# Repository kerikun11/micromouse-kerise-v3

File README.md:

# MicroMouse KERISE v3

ハーフサイズマイクロマウス

## 戦績

- 第38回全日本マイクロマウス大会2017
  - ハーフサイズ競技エキスパートクラス予選13位
  - ハーフサイズ競技エキスパートクラス決勝13位
  - ハーフサイズ競技エキスパートクラス特別賞

## スペック

| 部品             | 型番        | 備考                              |
| :--------------- | :---------- | :-------------------------------- |
| モーター         | 不明        | 直径6mm 長さ10mm コアレスモーター |
| エンコーダ       | AS5048A     | 4096パルス 磁気式                 |
| マイコン         | ESP32-D0WD  | 240MHz dual core                  |
| 赤外線LED        | VSMB294008G | 波長940mm                         |
| フォトダイオード | VEMD2020X01 | 波長940nm                         |
| モータードライバ | DRV8835     | 最大電流1.5A x 2ch                |
| 6軸センサ        | ICM-20602   | 3軸ジャイロ+3軸加速度             |
| バッテリー       | 不明        | 3.7V 25C 100mAh 1S                |

## 回路設計

- KiCad

## 開発環境

- ESP-IDF

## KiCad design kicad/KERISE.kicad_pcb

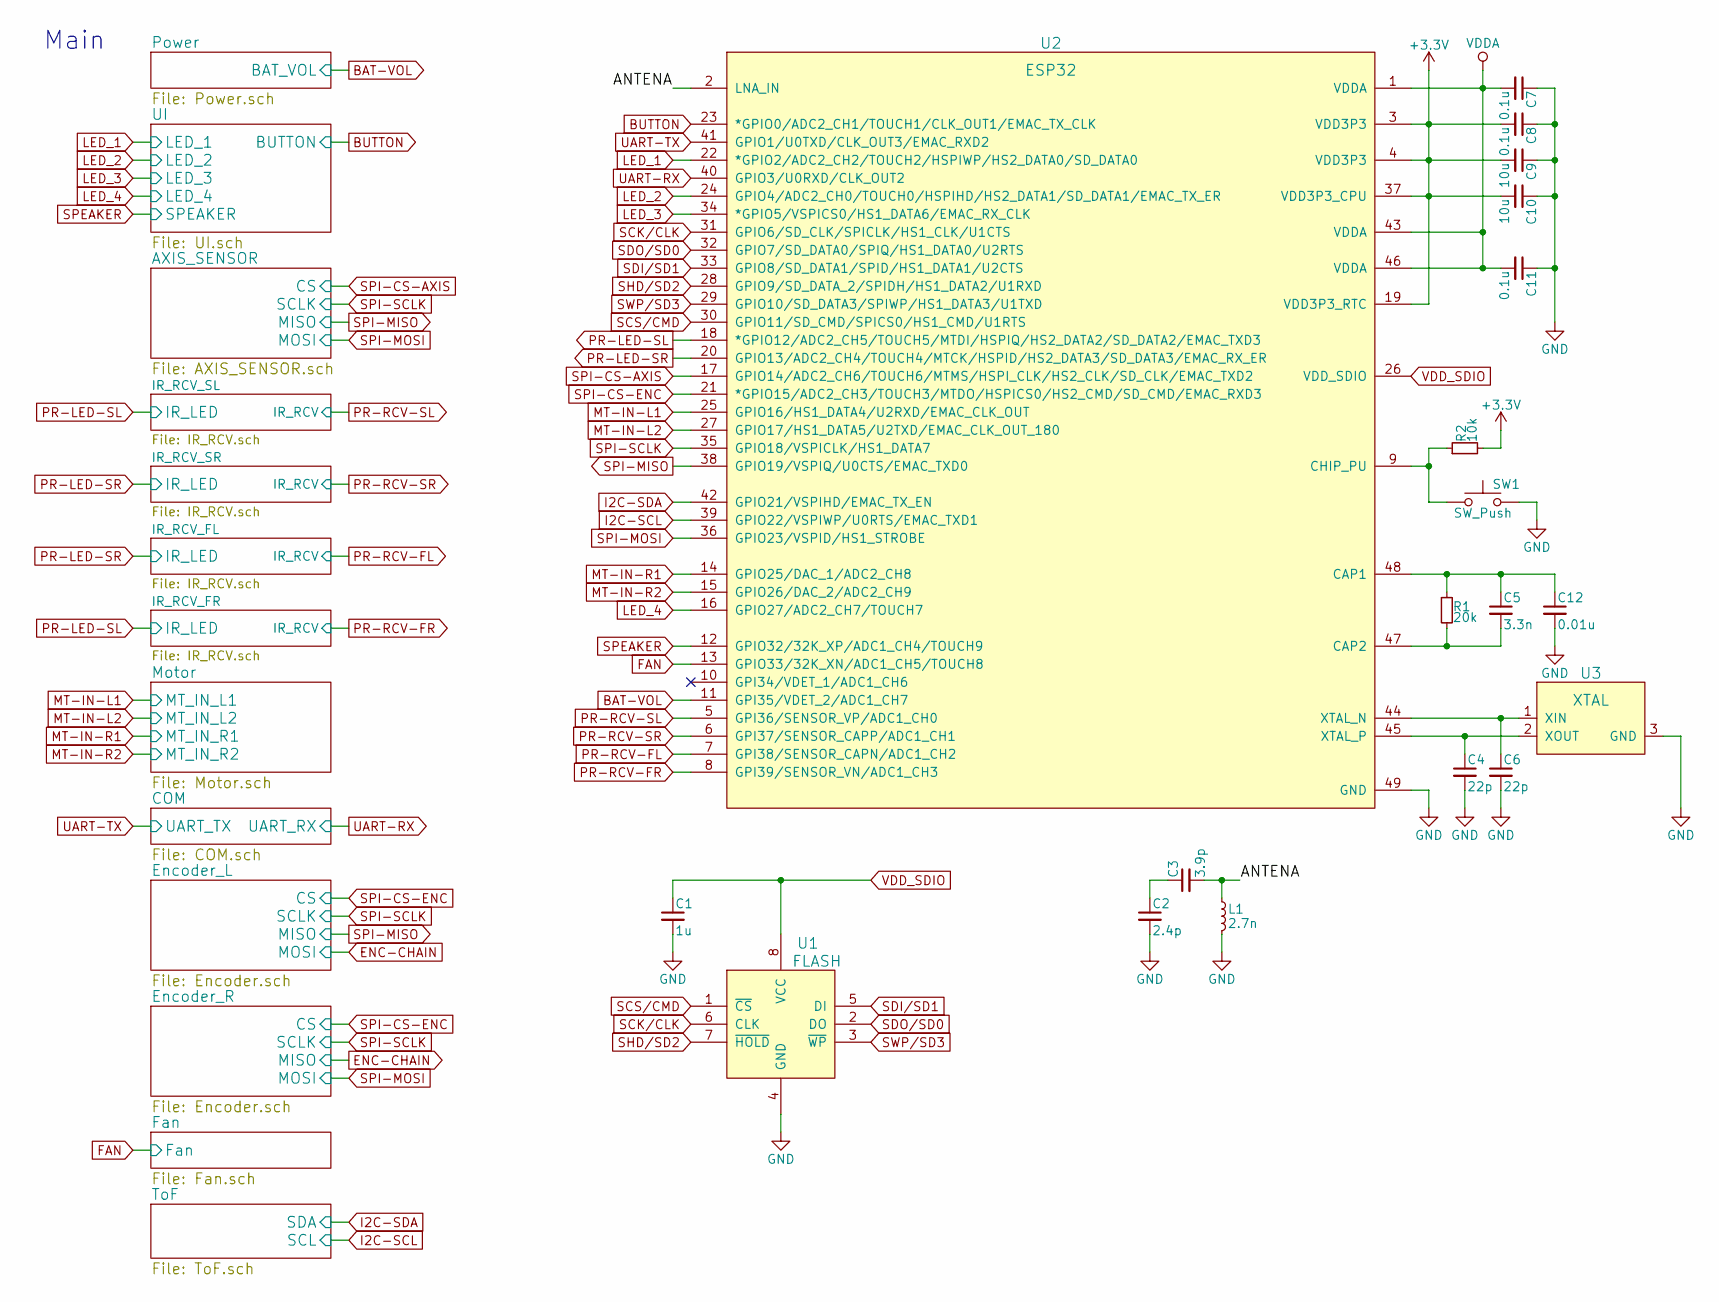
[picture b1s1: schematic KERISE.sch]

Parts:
C1: 1u; C_0402
C2: 2.4p; C_0201
C3: 3.9p; C_0201
C4, C6: 22p; C_0201
C5: 3.3n; C_0201
C7, C8, C11: 0.1u; C_0201
C9, C10: 10u; C_0402
C12: 0.01u; C_0201
L1: 2.7n; C_0201
R1: 20k; R_0201
R2: 10k; R_0201
SW1: SW_Push; SW_PUSH
U1: FLASH; SOIJ-8_5.3x5.3mm_Pitch1.27mm
U2: ESP32
U3: XTAL; crystal_FA238-TSX3225

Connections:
+3V3: C8.2, C9.2, C10.2, R2.2, U2.3 (VDD3P3), U2.4 (VDD3P3), U2.19 (VDD3P3_RTC), U2.37 (VDD3P3_CPU); also elsewhere on the board
/ANTENA: C3.2, L1.1, U2.2 (LNA_IN)
BAT-VOL: U2.11 (GPI35/VDET_2/ADC1_CH7); also elsewhere on the board
BUTTON: U2.23 (*GPIO0/ADC2_CH1/TOUCH1/CLK_OUT1/EMAC_TX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); also elsewhere on the board
FAN: U2.13 (GPIO33/32K_XN/ADC1_CH5/TOUCH8); also elsewhere on the board
GND: C1.2, C2.2, C4.2, C6.2, C7.1, C8.1, C9.1, C10.1, C11.1, C12.2, L1.2, SW1.2, U1.4 (GND), U2.49 (GND), U3.3 (GND); also elsewhere on the board
I2C-SCL: U2.39 (GPIO22/VSPIWP/U0RTS/EMAC_TXD1); also elsewhere on the board
I2C-SDA: U2.42 (GPIO21/VSPIHD/EMAC_TX_EN); also elsewhere on the board
LED_1: U2.22 (*GPIO2/ADC2_CH2/TOUCH2/HSPIWP/HS2_DATA0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); also elsewhere on the board
LED_2: U2.24 (GPIO4/ADC2_CH0/TOUCH0/HSPIHD/HS2_DATA1/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); also elsewhere on the board
LED_3: U2.34 (*GPIO5/VSPICS0/HS1_DATA6/EMAC_RX_CLK); also elsewhere on the board
LED_4: U2.16 (GPIO27/ADC2_CH7/TOUCH7); also elsewhere on the board
MT-IN-L1: U2.25 (GPIO16/HS1_DATA4/U2RXD/EMAC_CLK_OUT); also elsewhere on the board
MT-IN-L2: U2.27 (GPIO17/HS1_DATA5/U2TXD/EMAC_CLK_OUT_180); also elsewhere on the board
MT-IN-R1: U2.14 (GPIO25/DAC_1/ADC2_CH8); also elsewhere on the board
MT-IN-R2: U2.15 (GPIO26/DAC_2/ADC2_CH9); also elsewhere on the board
unnamed: C2.1, C3.1
unnamed: C4.1, U2.45 (XTAL_P), U3.2 (XOUT)
unnamed: C5.2, R1.2, U2.47 (CAP2)
unnamed: C6.1, U2.44 (XTAL_N), U3.1 (XIN)
unnamed: C5.1, C12.1, R1.1, U2.48 (CAP1)
unnamed: R2.1, SW1.1, U2.9 (CHIP_PU)
PR-LED-SL: U2.18 (*GPIO12/ADC2_CH5/TOUCH5/MTDI/HSPIQ/HS2_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); also elsewhere on the board
PR-LED-SR: U2.20 (GPIO13/ADC2_CH4/TOUCH4/MTCK/HSPID/HS2_D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); also elsewhere on the board
PR-RCV-FL: U2.7 (GPI38/SENSOR_CAPN/ADC1_CH2); also elsewhere on the board
PR-RCV-FR: U2.8 (GPI39/SENSOR_VN/ADC1_CH3); also elsewhere on the board
PR-RCV-SL: U2.5 (GPI36/SENSOR_VP/ADC1_CH0); also elsewhere on the board
PR-RCV-SR: U2.6 (GPI37/SENSOR_CAPP/ADC1_CH1); also elsewhere on the board
SCK/CLK: U1.6 (CLK), U2.31 (GPIO6/SD_CLK/SPICLK/HS1_CLK/U1CTS)
SCS/CMD: U1.1 (~CS), U2.30 (GPIO11/SD_CMD/SPICS0/HS1_CMD/U1RTS)
SDI/SD1: U1.5 (DI), U2.33 (GPIO8/SD_DATA1/SPID/HS1_DATA1/U2CTS)
SDO/SD0: U1.2 (DO), U2.32 (GPIO7/SD_DATA0/SPIQ/HS1_DATA0/U2RTS)
SHD/SD2: U1.7 (~HOLD), U2.28 (GPIO9/SD_DATA_2/SPIDH/HS1_DATA2/U1RXD)
SPEAKER: U2.12 (GPIO32/32K_XP/ADC1_CH4/TOUCH9); also elsewhere on the board
SPI-CS-AXIS: U2.17 (GPIO14/ADC2_CH6/TOUCH6/MTMS/HSPI_CLK/HS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); also elsewhere on the board
SPI-CS-ENC: U2.21 (*GPIO15/ADC2_CH3/TOUCH3/MTDO/HSPICS0/HS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); also elsewhere on the board
SPI-MISO: U2.38 (GPIO19/VSPIQ/U0CTS/EMAC_TXD0); also elsewhere on the board
SPI-MOSI: U2.36 (GPIO23/VSPID/HS1_STROBE); also elsewhere on the board
SPI-SCLK: U2.35 (GPIO18/VSPICLK/HS1_DATA7); also elsewhere on the board
SWP/SD3: U1.3 (~WP), U2.29 (GPIO10/SD_DATA3/SPIWP/HS1_DATA3/U1TXD)
UART-RX: U2.40 (GPIO3/U0RXD/CLK_OUT2); also elsewhere on the board
UART-TX: U2.41 (GPIO1/U0TXD/CLK_OUT3/EMAC_RXD2); also elsewhere on the board
VDDA: C7.2, C11.2, U2.1 (VDDA), U2.43 (VDDA), U2.46 (VDDA); also elsewhere on the board
VDD_SDIO: C1.1, U1.8 (VCC), U2.26 (VDD_SDIO)

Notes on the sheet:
Main

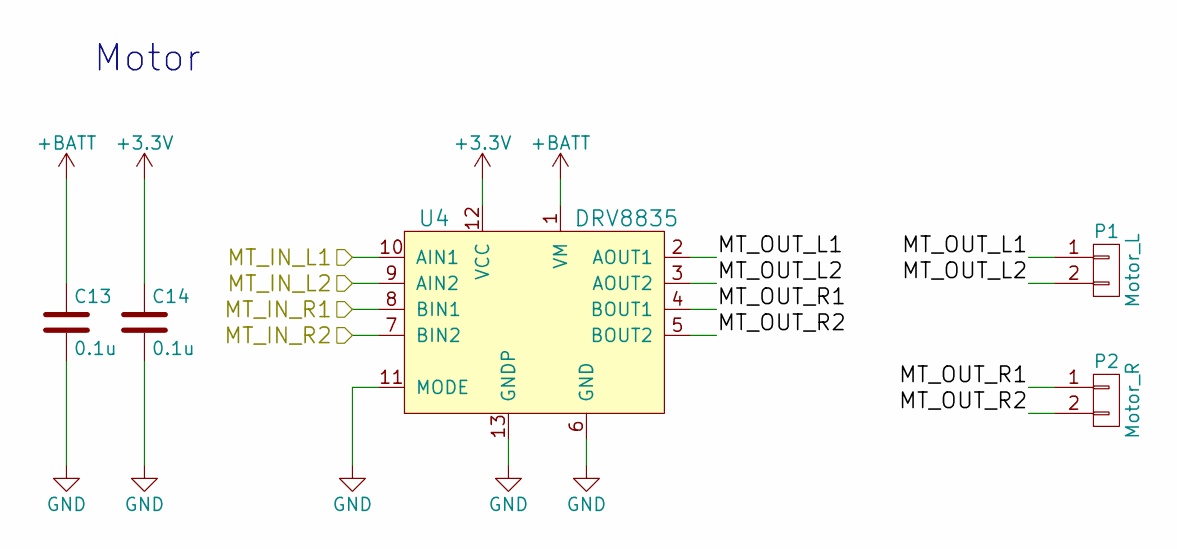
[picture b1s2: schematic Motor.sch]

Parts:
C13, C14: 0.1u; C_0201
P1: Motor_L; SMD_conn_2
P2: Motor_R; SMD_conn_2
U4: DRV8835

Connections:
+3V3: C14.1, U4.12 (VCC); also elsewhere on the board
+BATT: C13.1, U4.1 (VM); also elsewhere on the board
/Motor/MT_OUT_L1: P1.1, U4.2 (AOUT1)
/Motor/MT_OUT_L2: P1.2, U4.3 (AOUT2)
/Motor/MT_OUT_R1: P2.1, U4.4 (BOUT1)
/Motor/MT_OUT_R2: P2.2, U4.5 (BOUT2)
GND: C13.2, C14.2, U4.6 (GND), U4.11 (MODE), U4.13 (GNDP); also elsewhere on the board
MT-IN-L1: U4.10 (AIN1); also elsewhere on the board
MT-IN-L2: U4.9 (AIN2); also elsewhere on the board
MT-IN-R1: U4.8 (BIN1); also elsewhere on the board
MT-IN-R2: U4.7 (BIN2); also elsewhere on the board

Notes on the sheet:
Motor

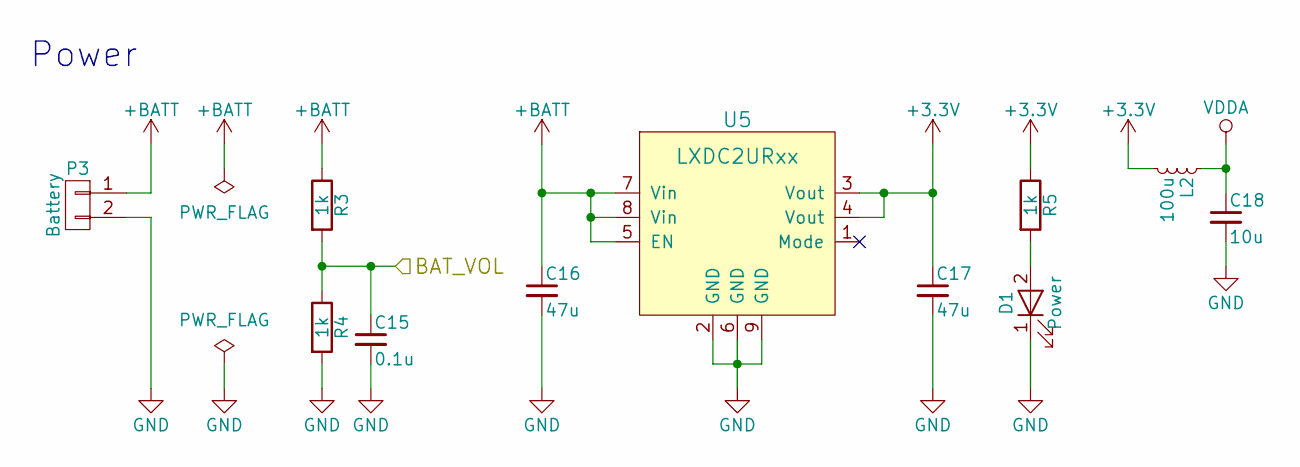
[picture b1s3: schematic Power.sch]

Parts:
C15: 0.1u; C_0201
C16, C17: 47u; C_0805
C18: 10u; C_0402
D1: Power; LED_0402
L2: 100u; C_0603
P3: Battery; Hirose_DF13-02P-1.25DSA_02x1.25mm_Straight
R3, R4, R5: 1k; R_0201
U5: LXDC2URxx; LXDC2UR

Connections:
+3V3: C17.1, L2.2, R5.1, U5.3 (Vout), U5.4 (Vout); also elsewhere on the board
+BATT: C16.1, P3.1, R3.1, U5.5 (EN), U5.7 (Vin), U5.8 (Vin); also elsewhere on the board
BAT-VOL: C15.1, R3.2, R4.1; also elsewhere on the board
GND: C15.2, C16.2, C17.2, C18.2, D1.1 (K), P3.2, R4.2, U5.2 (GND), U5.6 (GND), U5.9 (GND); also elsewhere on the board
unnamed: D1.2 (A), R5.2
VDDA: C18.1, L2.1; also elsewhere on the board

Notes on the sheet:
Power

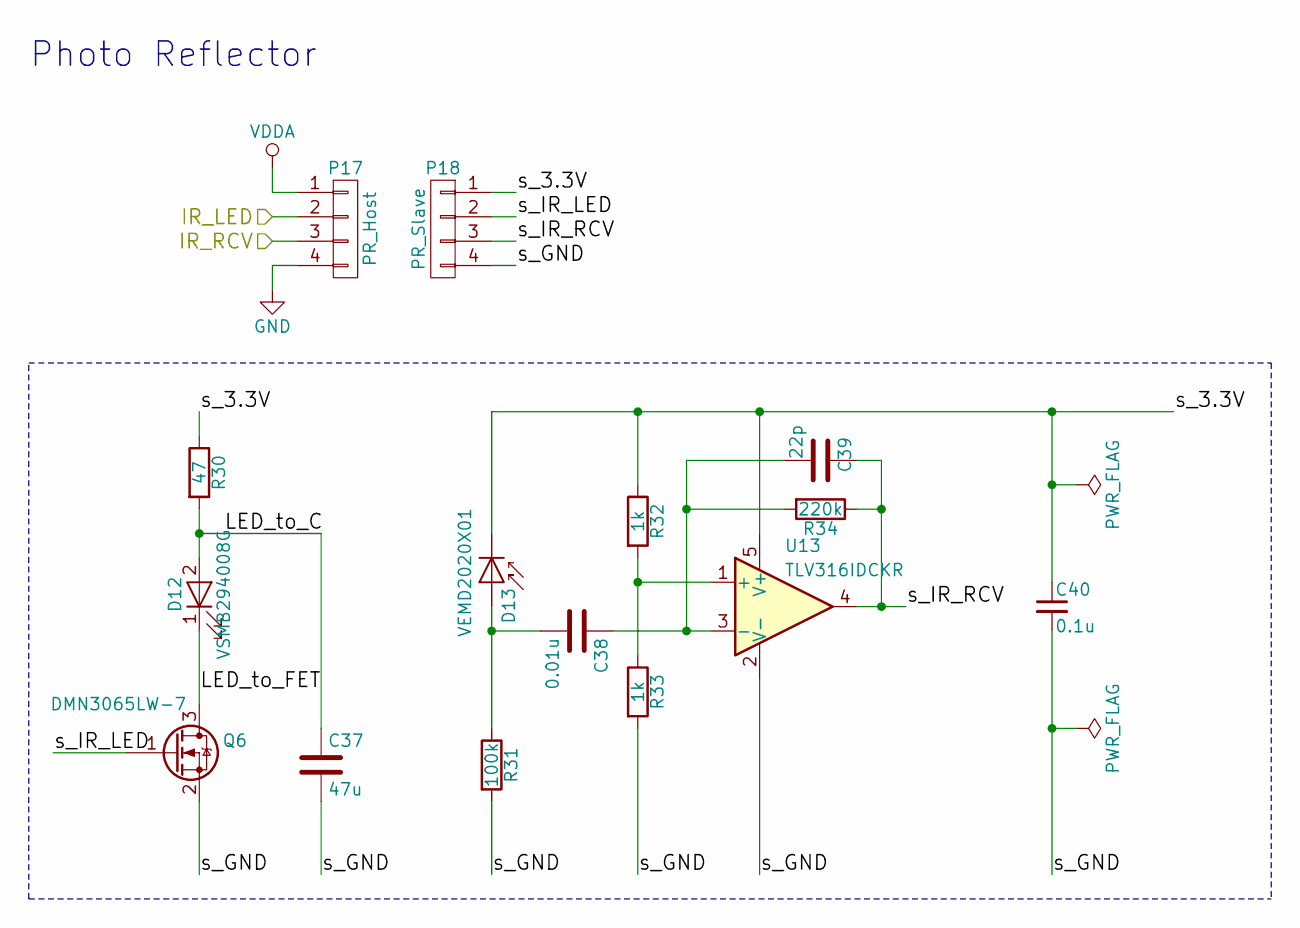
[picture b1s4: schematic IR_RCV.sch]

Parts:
C19: 47u; C_0805
C20: 0.01u; C_0201
C21: 22p; C_0201
C22: 0.1u; C_0201
D2: VSMB294008G; VISHAY_DIODE
D3: VEMD2020X01; VISHAY_DIODE
P4: PR_Host; STAND_PR_HOST
P5: PR_Slave; STAND_PR_SLAVE
Q1: DMN3065LW-7; SOT-323_SC-70
R6: 47; R_0603
R7: 100k; R_0201
R8, R9: 1k; R_0201
R10: 220k; R_0201
U6: TLV316IDCKR; SOT-353_SC-70-5

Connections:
/IR_RCV_SL/LED_to_C: C19.1, D2.2 (A), R6.2
/IR_RCV_SL/LED_to_FET: D2.1 (K), Q1.3 (D)
/IR_RCV_SL/s_3.3V: C22.1, D3.1 (K), P5.1, R6.1, R8.1, U6.5 (V+)
/IR_RCV_SL/s_GND: C19.2, C22.2, P5.4, Q1.2 (S), R7.2, R9.2, U6.2 (V-)
/IR_RCV_SL/s_IR_LED: P5.2, Q1.1 (G)
/IR_RCV_SL/s_IR_RCV: C21.1, P5.3, R10.1, U6.4
GND: P4.4; also elsewhere on the board
unnamed: C20.1, C21.2, R10.2, U6.3 (-)
unnamed: C20.2, D3.2 (A), R7.1
unnamed: R8.2, R9.1, U6.1 (+)
PR-LED-SL: P4.2; also elsewhere on the board
PR-RCV-SL: P4.3; also elsewhere on the board
VDDA: P4.1; also elsewhere on the board

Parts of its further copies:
C23, C33, C37: 47u; C_0805
C24, C34, C38: 0.01u; C_0201
C25, C35, C39: 22p; C_0201
C26, C36, C40: 0.1u; C_0201
D4, D10, D12: VSMB294008G; VISHAY_DIODE
D5, D11, D13: VEMD2020X01; VISHAY_DIODE
P6, P15, P17: PR_Host; STAND_PR_HOST
P7, P16, P18: PR_Slave; STAND_PR_SLAVE
Q2, Q5, Q6: DMN3065LW-7; SOT-323_SC-70
R11, R25, R30: 47; R_0603
R12, R26, R31: 100k; R_0201
R13, R14, R27, R28, R32, R33: 1k; R_0201
R15, R29, R34: 220k; R_0201
U7, U12, U13: TLV316IDCKR; SOT-353_SC-70-5

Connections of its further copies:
/IR_RCV_FL/LED_to_C: C33.1, D10.2 (A), R25.2
/IR_RCV_FL/LED_to_FET: D10.1 (K), Q5.3 (D)
/IR_RCV_FL/s_3.3V: C36.1, D11.1 (K), P16.1, R25.1, R27.1, U12.5 (V+)
/IR_RCV_FL/s_GND: C33.2, C36.2, P16.4, Q5.2 (S), R26.2, R28.2, U12.2 (V-)
/IR_RCV_FL/s_IR_LED: P16.2, Q5.1 (G)
/IR_RCV_FL/s_IR_RCV: C35.1, P16.3, R29.1, U12.4
/IR_RCV_FR/LED_to_C: C37.1, D12.2 (A), R30.2
/IR_RCV_FR/LED_to_FET: D12.1 (K), Q6.3 (D)
/IR_RCV_FR/s_3.3V: C40.1, D13.1 (K), P18.1, R30.1, R32.1, U13.5 (V+)
/IR_RCV_FR/s_GND: C37.2, C40.2, P18.4, Q6.2 (S), R31.2, R33.2, U13.2 (V-)
/IR_RCV_FR/s_IR_LED: P18.2, Q6.1 (G)
/IR_RCV_FR/s_IR_RCV: C39.1, P18.3, R34.1, U13.4
/IR_RCV_SR/LED_to_C: C23.1, D4.2 (A), R11.2
/IR_RCV_SR/LED_to_FET: D4.1 (K), Q2.3 (D)
/IR_RCV_SR/s_3.3V: C26.1, D5.1 (K), P7.1, R11.1, R13.1, U7.5 (V+)
/IR_RCV_SR/s_GND: C23.2, C26.2, P7.4, Q2.2 (S), R12.2, R14.2, U7.2 (V-)
/IR_RCV_SR/s_IR_LED: P7.2, Q2.1 (G)
/IR_RCV_SR/s_IR_RCV: C25.1, P7.3, R15.1, U7.4
GND: P6.4, P15.4, P17.4; also elsewhere on the board
unnamed: C24.1, C25.2, R15.2, U7.3 (-)
unnamed: C24.2, D5.2 (A), R12.1
unnamed: C34.1, C35.2, R29.2, U12.3 (-)
unnamed: C34.2, D11.2 (A), R26.1
unnamed: C38.1, C39.2, R34.2, U13.3 (-)
unnamed: C38.2, D13.2 (A), R31.1
unnamed: R13.2, R14.1, U7.1 (+)
unnamed: R27.2, R28.1, U12.1 (+)
unnamed: R32.2, R33.1, U13.1 (+)
PR-LED-SL: P17.2; also elsewhere on the board
PR-LED-SR: P6.2, P15.2; also elsewhere on the board
PR-RCV-FL: P15.3; also elsewhere on the board
PR-RCV-FR: P17.3; also elsewhere on the board
PR-RCV-SR: P6.3; also elsewhere on the board
VDDA: P6.1, P15.1, P17.1; also elsewhere on the board

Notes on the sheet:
Photo Reflector

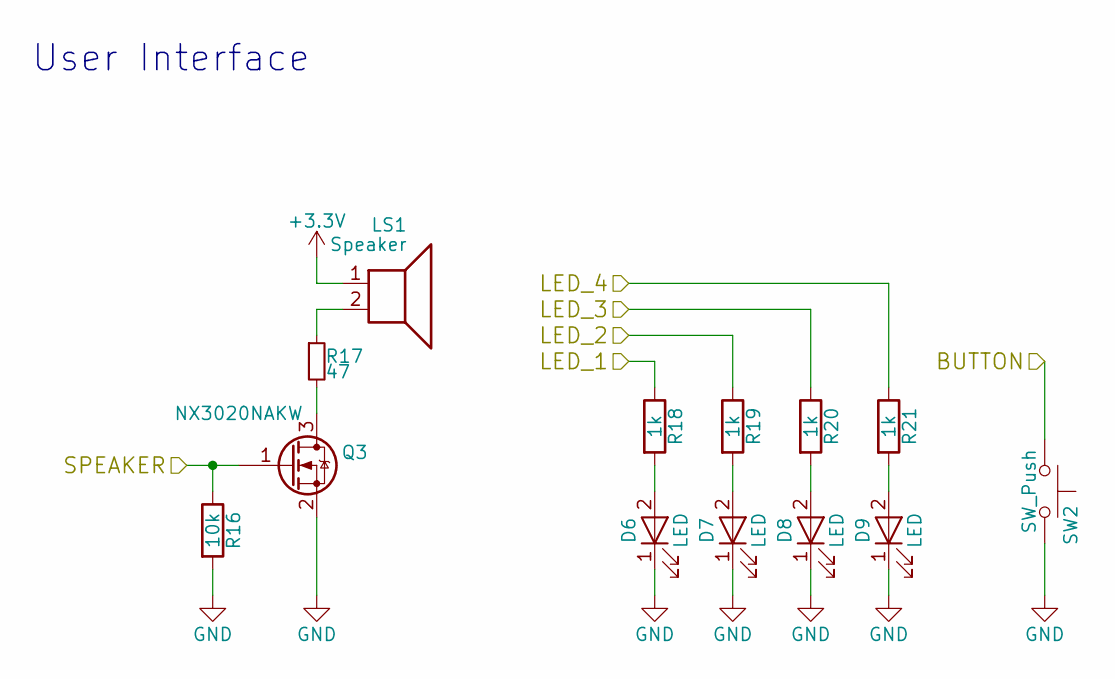
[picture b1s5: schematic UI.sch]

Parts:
D6, D7, D8, D9: LED; LED_0402
LS1: Speaker; SMT-0440-S-R
Q3: NX3020NAKW; SOT-323_SC-70
R16: 10k; R_0201
R17: 47; R_0201
R18, R19, R20, R21: 1k; R_0201
SW2: SW_Push; SW_PUSH

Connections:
+3V3: LS1.1; also elsewhere on the board
BUTTON: SW2.1; also elsewhere on the board
GND: D6.1 (K), D7.1 (K), D8.1 (K), D9.1 (K), Q3.2 (S), R16.2, SW2.2; also elsewhere on the board
LED_1: R18.1; also elsewhere on the board
LED_2: R19.1; also elsewhere on the board
LED_3: R20.1; also elsewhere on the board
LED_4: R21.1; also elsewhere on the board
unnamed: D6.2 (A), R18.2
unnamed: D7.2 (A), R19.2
unnamed: D8.2 (A), R20.2
unnamed: D9.2 (A), R21.2
unnamed: LS1.2, R17.1
unnamed: Q3.3 (D), R17.2
SPEAKER: Q3.1 (G), R16.1; also elsewhere on the board

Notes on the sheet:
User Interface

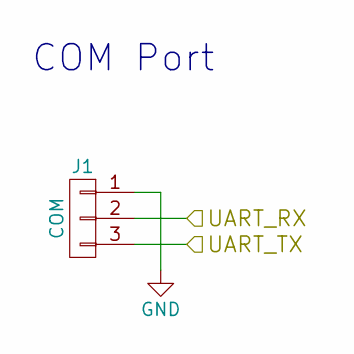
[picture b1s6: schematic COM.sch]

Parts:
J1: COM; JST_SH_BM03B-SRSS-TB_03x1.00mm_Straight

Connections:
GND: J1.1; also elsewhere on the board
UART-RX: J1.2; also elsewhere on the board
UART-TX: J1.3; also elsewhere on the board

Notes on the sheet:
COM Port

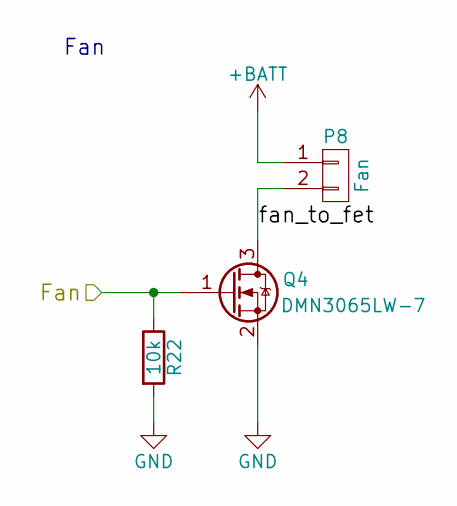
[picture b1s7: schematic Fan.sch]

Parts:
P8: Fan; SMD_conn_2
Q4: DMN3065LW-7; SOT-323_SC-70
R22: 10k; R_0201

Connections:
+BATT: P8.1; also elsewhere on the board
/Fan/fan_to_fet: P8.2, Q4.3 (D)
FAN: Q4.1 (G), R22.1; also elsewhere on the board
GND: Q4.2 (S), R22.2; also elsewhere on the board

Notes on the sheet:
Fan

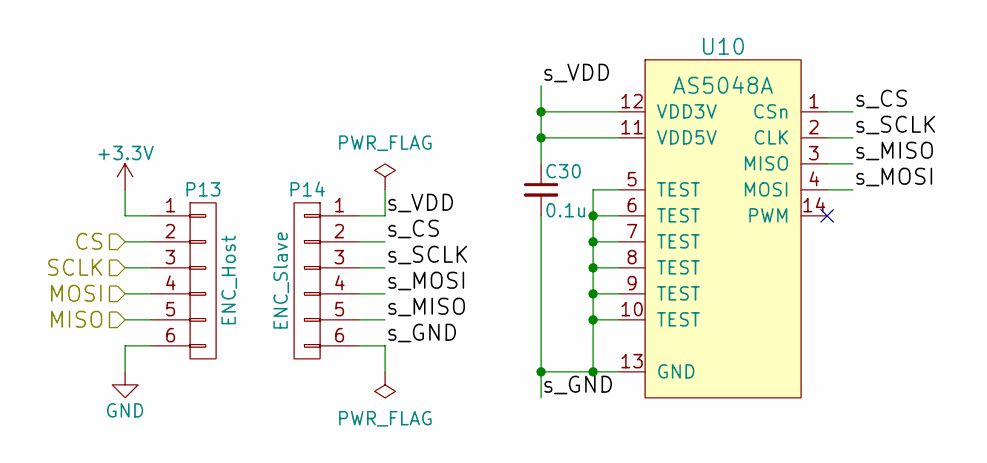
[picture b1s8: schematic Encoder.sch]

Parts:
C27: 0.1u; C_0201
P9: ENC_Host; STAND_AS_HOST
P10: ENC_Slave; STAND_AS_SLAVE
U8: AS5048A; TSSOP-14_4.4x5mm_Pitch0.65mm

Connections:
+3V3: P9.1; also elsewhere on the board
/Encoder_R/s_CS: P10.2, U8.1 (CSn)
/Encoder_R/s_GND: C27.2, P10.6, U8.5 (TEST), U8.6 (TEST), U8.7 (TEST), U8.8 (TEST), U8.9 (TEST), U8.10 (TEST), U8.13 (GND)
/Encoder_R/s_MISO: P10.5, U8.3 (MISO)
/Encoder_R/s_MOSI: P10.4, U8.4 (MOSI)
/Encoder_R/s_SCLK: P10.3, U8.2 (CLK)
/Encoder_R/s_VDD: C27.1, P10.1, U8.11 (VDD5V), U8.12 (VDD3V)
ENC-CHAIN: P9.5; also elsewhere on the board
GND: P9.6; also elsewhere on the board
SPI-CS-ENC: P9.2; also elsewhere on the board
SPI-MOSI: P9.4; also elsewhere on the board
SPI-SCLK: P9.3; also elsewhere on the board

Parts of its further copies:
C30: 0.1u; C_0201
P13: ENC_Host; STAND_AS_HOST
P14: ENC_Slave; STAND_AS_SLAVE
U10: AS5048A; TSSOP-14_4.4x5mm_Pitch0.65mm

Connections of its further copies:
+3V3: P13.1; also elsewhere on the board
/Encoder_L/s_CS: P14.2, U10.1 (CSn)
/Encoder_L/s_GND: C30.2, P14.6, U10.5 (TEST), U10.6 (TEST), U10.7 (TEST), U10.8 (TEST), U10.9 (TEST), U10.10 (TEST), U10.13 (GND)
/Encoder_L/s_MISO: P14.5, U10.3 (MISO)
/Encoder_L/s_MOSI: P14.4, U10.4 (MOSI)
/Encoder_L/s_SCLK: P14.3, U10.2 (CLK)
/Encoder_L/s_VDD: C30.1, P14.1, U10.11 (VDD5V), U10.12 (VDD3V)
ENC-CHAIN: P13.4; also elsewhere on the board
GND: P13.6; also elsewhere on the board
SPI-CS-ENC: P13.2; also elsewhere on the board
SPI-MISO: P13.5; also elsewhere on the board
SPI-SCLK: P13.3; also elsewhere on the board

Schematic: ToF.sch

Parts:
C28: 4.7u; C_0402
C29: 0.1u; C_0201
P11: ToF_Host; STAND_PR_HOST
P12: ToF_Slave; STAND_PR_SLAVE
R23, R24: 4.7k; R_0201
U9: VL53L0X

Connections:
+3V3: P11.1; also elsewhere on the board
/ToF/s_3.3V: C28.1, C29.1, P12.1, R23.1, R24.1, U9.1 (AVDDVCSEL), U9.5 (XSHUT), U9.11 (AVDD)
/ToF/s_GND: C28.2, C29.2, P12.4, U9.2 (AVSSVCSEL), U9.3 (GND), U9.4 (GND2), U9.6 (GND3), U9.12 (GND4)
/ToF/s_SCL: P12.3, R24.2, U9.10 (SCL)
/ToF/s_SDA: P12.2, R23.2, U9.9 (SDA)
GND: P11.4; also elsewhere on the board
I2C-SCL: P11.3; also elsewhere on the board
I2C-SDA: P11.2; also elsewhere on the board

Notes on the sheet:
ToF

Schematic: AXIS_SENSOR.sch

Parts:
C31, C32: 0.1u; C_0201
U11: ICM-20602; LGA-16-3x3

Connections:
+3V3: C31.1, U11.1 (VDDIO), U11.16 (VDD); also elsewhere on the board
GND: C31.2, C32.2, U11.8 (FSYNC), U11.9 (RESV), U11.10 (RESV), U11.11 (RESV), U11.12 (RESV), U11.13 (GND), U11.15 (RESV); also elsewhere on the board
unnamed: C32.1, U11.14 (REGOUT)
SPI-CS-AXIS: U11.5 (CS); also elsewhere on the board
SPI-MISO: U11.4 (SA0/SDO); also elsewhere on the board
SPI-MOSI: U11.3 (SDA/SDI); also elsewhere on the board
SPI-SCLK: U11.2 (SCL/SPC); also elsewhere on the board

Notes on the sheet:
AXIS Sensor

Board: 2 copper layers, 130 parts (32 on the bottom side), 111 nets, no tracks yet.

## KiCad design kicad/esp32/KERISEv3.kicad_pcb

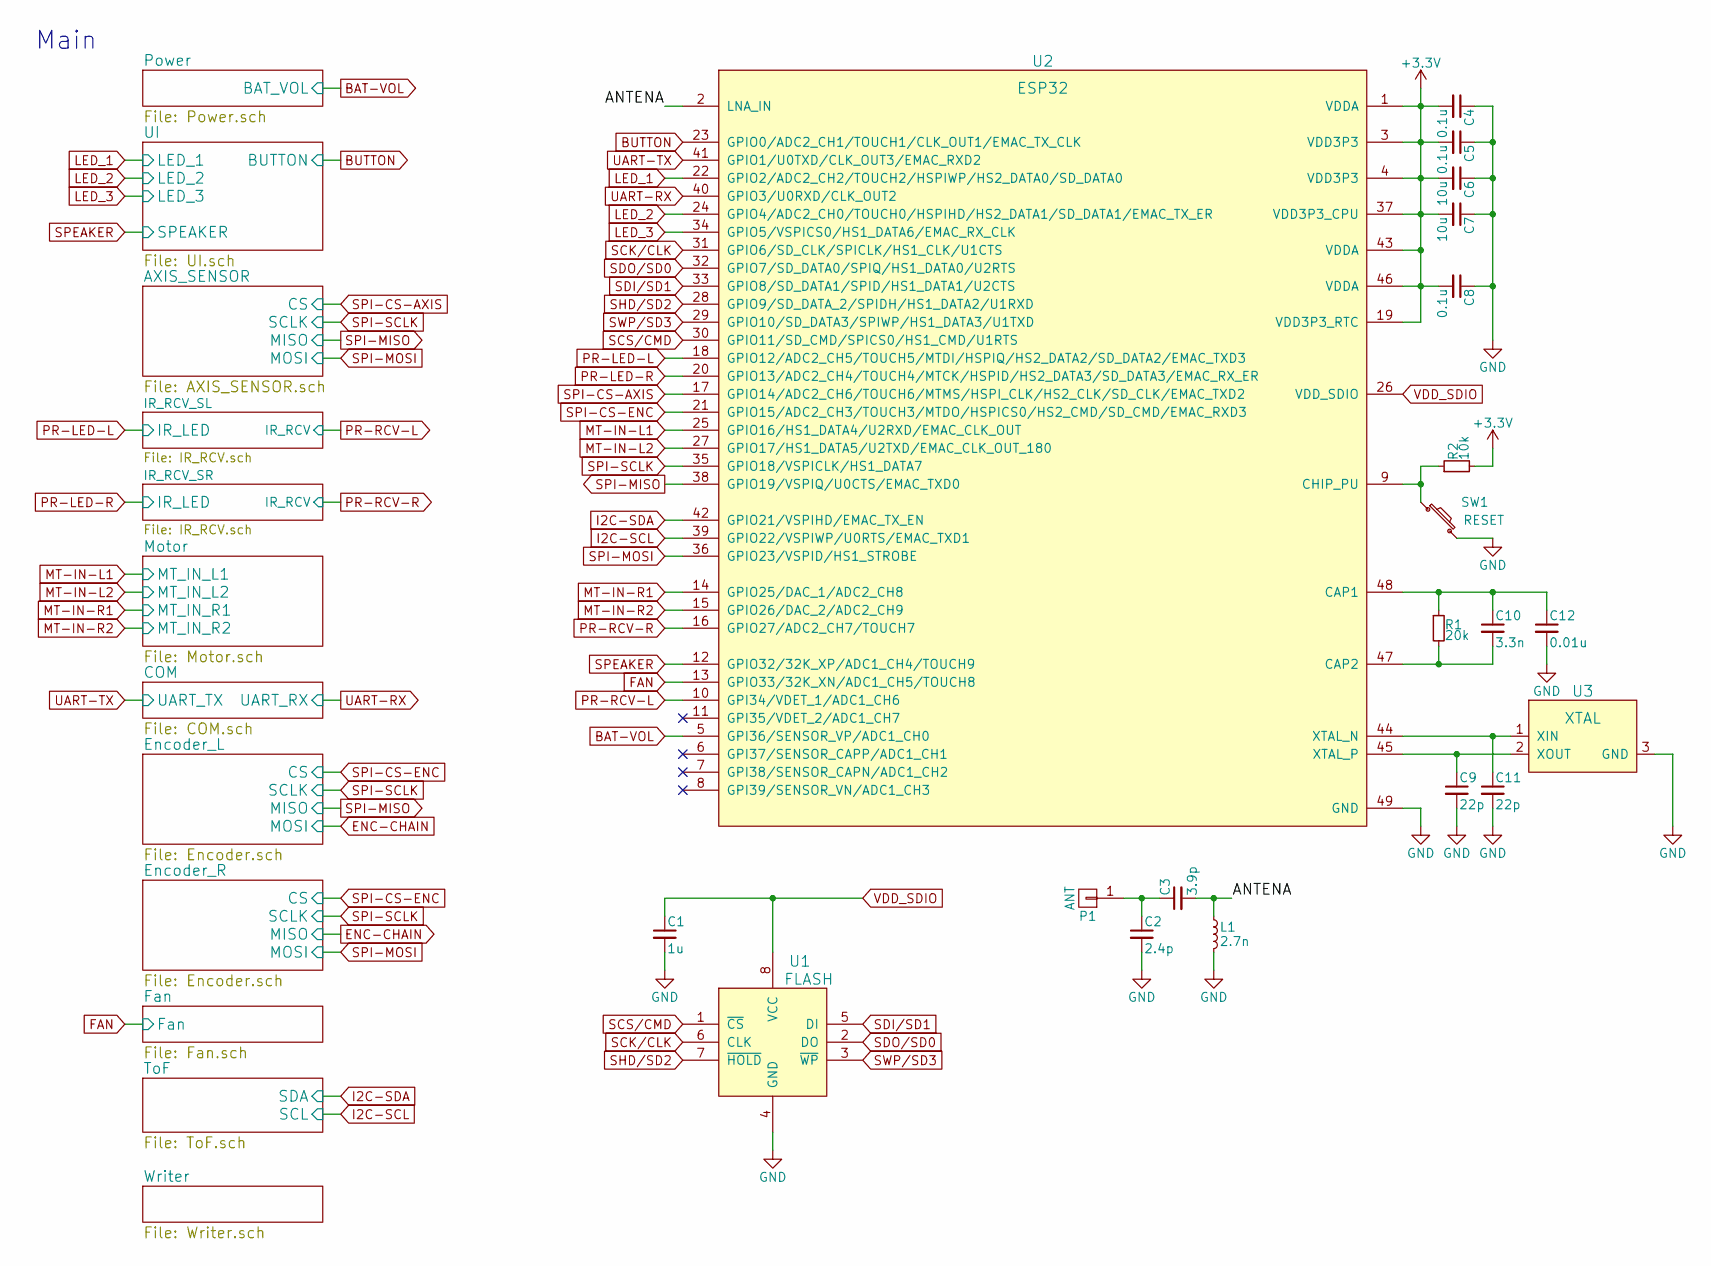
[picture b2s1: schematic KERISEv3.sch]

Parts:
C1: 1u; C_0402
C2: 2.4p; C_0201
C3: 3.9p; C_0201
C4, C5, C8: 0.1u; C_0201
C6, C7: 10u; C_0402
C9, C11: 22p; C_0201
C10: 3.3n; C_0201
C12: 0.01u; C_0201
L1: 2.7n; C_0201
P1: ANT; SMD_conn_1
R1: 20k; R_0201
R2: 10k; R_0201
SW1: RESET; SW_PUSH
U1: FLASH; DFN-8-1EP_6x5mm_Pitch1.27mm_SmallFlag
U2: ESP32
U3: XTAL; crystal_FA238-TSX3225

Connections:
+3V3: C4.2, C5.2, C6.2, C7.2, C8.2, R2.2, U2.1 (VDDA), U2.3 (VDD3P3), U2.4 (VDD3P3), U2.19 (VDD3P3_RTC), U2.37 (VDD3P3_CPU), U2.43 (VDDA), U2.46 (VDDA); also elsewhere on the board
/ANTENA: C3.2, L1.1, U2.2 (LNA_IN)
BAT-VOL: U2.5 (GPI36/SENSOR_VP/ADC1_CH0); also elsewhere on the board
BUTTON: U2.23 (GPIO0/ADC2_CH1/TOUCH1/CLK_OUT1/EMAC_TX_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); also elsewhere on the board
FAN: U2.13 (GPIO33/32K_XN/ADC1_CH5/TOUCH8); also elsewhere on the board
GND: C1.2, C2.2, C4.1, C5.1, C6.1, C7.1, C8.1, C9.2, C11.2, C12.2, L1.2, SW1.2, U1.4 (GND), U2.49 (GND), U3.3 (GND); also elsewhere on the board
I2C-SCL: U2.39 (GPIO22/VSPIWP/U0RTS/EMAC_TXD1); also elsewhere on the board
I2C-SDA: U2.42 (GPIO21/VSPIHD/EMAC_TX_EN); also elsewhere on the board
LED_1: U2.22 (GPIO2/ADC2_CH2/TOUCH2/HSPIWP/HS2_DATA0/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); also elsewhere on the board
LED_2: U2.24 (GPIO4/ADC2_CH0/TOUCH0/HSPIHD/HS2_DATA1/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); also elsewhere on the board
LED_3: U2.34 (GPIO5/VSPICS0/HS1_DATA6/EMAC_RX_CLK); also elsewhere on the board
MT-IN-L1: U2.25 (GPIO16/HS1_DATA4/U2RXD/EMAC_CLK_OUT); also elsewhere on the board
MT-IN-L2: U2.27 (GPIO17/HS1_DATA5/U2TXD/EMAC_CLK_OUT_180); also elsewhere on the board
MT-IN-R1: U2.14 (GPIO25/DAC_1/ADC2_CH8); also elsewhere on the board
MT-IN-R2: U2.15 (GPIO26/DAC_2/ADC2_CH9); also elsewhere on the board
unnamed: C2.1, C3.1, P1.1
unnamed: C9.1, U2.45 (XTAL_P), U3.2 (XOUT)
unnamed: C10.1, C12.1, R1.1, U2.48 (CAP1)
unnamed: C10.2, R1.2, U2.47 (CAP2)
unnamed: C11.1, U2.44 (XTAL_N), U3.1 (XIN)
unnamed: R2.1, SW1.1, U2.9 (CHIP_PU)
PR-LED-L: U2.18 (GPIO12/ADC2_CH5/TOUCH5/MTDI/HSPIQ/HS2_D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); also elsewhere on the board
PR-LED-R: U2.20 (GPIO13/ADC2_CH4/TOUCH4/MTCK/HSPID/HS2_D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); also elsewhere on the board
PR-RCV-L: U2.10 (GPI34/VDET_1/ADC1_CH6); also elsewhere on the board
PR-RCV-R: U2.16 (GPIO27/ADC2_CH7/TOUCH7); also elsewhere on the board
SCK/CLK: U1.6 (CLK), U2.31 (GPIO6/SD_CLK/SPICLK/HS1_CLK/U1CTS)
SCS/CMD: U1.1 (~CS), U2.30 (GPIO11/SD_CMD/SPICS0/HS1_CMD/U1RTS)
SDI/SD1: U1.5 (DI), U2.33 (GPIO8/SD_DATA1/SPID/HS1_DATA1/U2CTS)
SDO/SD0: U1.2 (DO), U2.32 (GPIO7/SD_DATA0/SPIQ/HS1_DATA0/U2RTS)
SHD/SD2: U1.7 (~HOLD), U2.28 (GPIO9/SD_DATA_2/SPIDH/HS1_DATA2/U1RXD)
SPEAKER: U2.12 (GPIO32/32K_XP/ADC1_CH4/TOUCH9); also elsewhere on the board
SPI-CS-AXIS: U2.17 (GPIO14/ADC2_CH6/TOUCH6/MTMS/HSPI_CLK/HS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); also elsewhere on the board
SPI-CS-ENC: U2.21 (GPIO15/ADC2_CH3/TOUCH3/MTDO/HSPICS0/HS2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); also elsewhere on the board
SPI-MISO: U2.38 (GPIO19/VSPIQ/U0CTS/EMAC_TXD0); also elsewhere on the board
SPI-MOSI: U2.36 (GPIO23/VSPID/HS1_STROBE); also elsewhere on the board
SPI-SCLK: U2.35 (GPIO18/VSPICLK/HS1_DATA7); also elsewhere on the board
SWP/SD3: U1.3 (~WP), U2.29 (GPIO10/SD_DATA3/SPIWP/HS1_DATA3/U1TXD)
UART-RX: U2.40 (GPIO3/U0RXD/CLK_OUT2); also elsewhere on the board
UART-TX: U2.41 (GPIO1/U0TXD/CLK_OUT3/EMAC_RXD2); also elsewhere on the board
VDD_SDIO: C1.1, U1.8 (VCC), U2.26 (VDD_SDIO)

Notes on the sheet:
Main

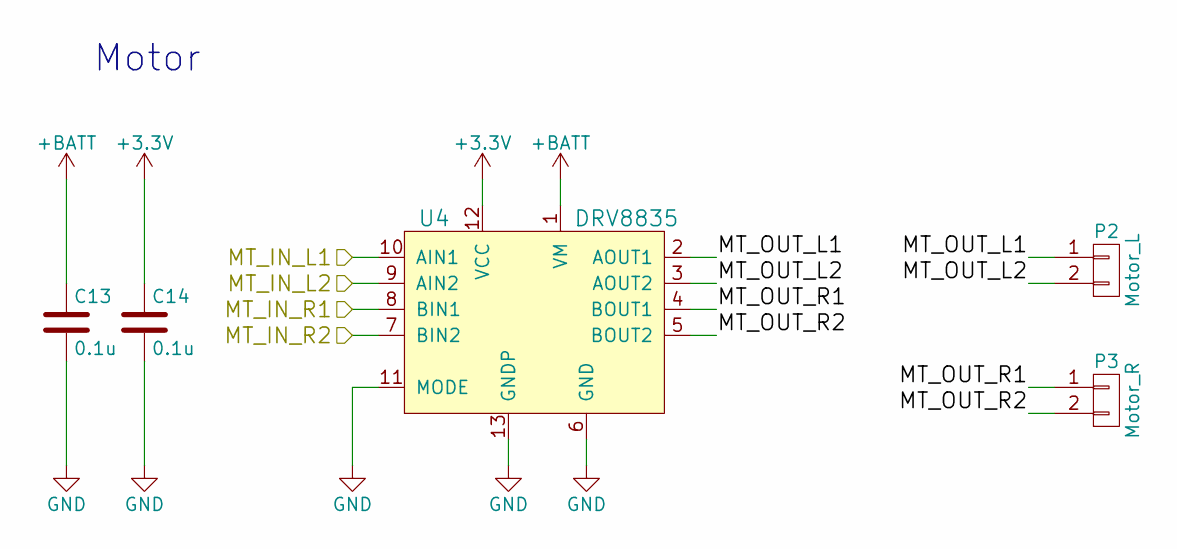
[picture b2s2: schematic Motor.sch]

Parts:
C13, C14: 0.1u; C_0201
P2: Motor_L; SMD_conn_2
P3: Motor_R; SMD_conn_2
U4: DRV8835

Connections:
+3V3: C14.1, U4.12 (VCC); also elsewhere on the board
+BATT: C13.1, U4.1 (VM); also elsewhere on the board
/Motor/MT_OUT_L1: P2.1, U4.2 (AOUT1)
/Motor/MT_OUT_L2: P2.2, U4.3 (AOUT2)
/Motor/MT_OUT_R1: P3.1, U4.4 (BOUT1)
/Motor/MT_OUT_R2: P3.2, U4.5 (BOUT2)
GND: C13.2, C14.2, U4.6 (GND), U4.11 (MODE), U4.13 (GNDP); also elsewhere on the board
MT-IN-L1: U4.10 (AIN1); also elsewhere on the board
MT-IN-L2: U4.9 (AIN2); also elsewhere on the board
MT-IN-R1: U4.8 (BIN1); also elsewhere on the board
MT-IN-R2: U4.7 (BIN2); also elsewhere on the board

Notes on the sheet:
Motor

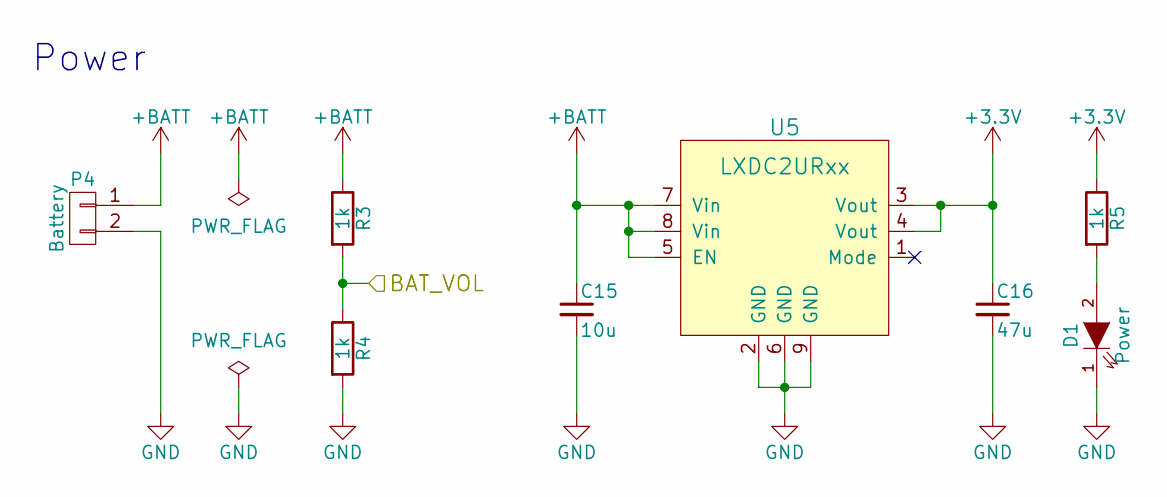
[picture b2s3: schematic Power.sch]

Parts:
C15: 10u; C_0603
C16: 47u; C_0805
D1: Power; LED_0402
P4: Battery; Hirose_DF13-02P-1.25DSA_02x1.25mm_Straight
R3, R4, R5: 1k; R_0201
U5: LXDC2URxx; LXDC2UR

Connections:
+3V3: C16.1, R5.1, U5.3 (Vout), U5.4 (Vout); also elsewhere on the board
+BATT: C15.1, P4.1, R3.1, U5.5 (EN), U5.7 (Vin), U5.8 (Vin); also elsewhere on the board
BAT-VOL: R3.2, R4.1; also elsewhere on the board
GND: C15.2, C16.2, D1.1 (K), P4.2, R4.2, U5.2 (GND), U5.6 (GND), U5.9 (GND); also elsewhere on the board
unnamed: D1.2 (A), R5.2

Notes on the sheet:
Power

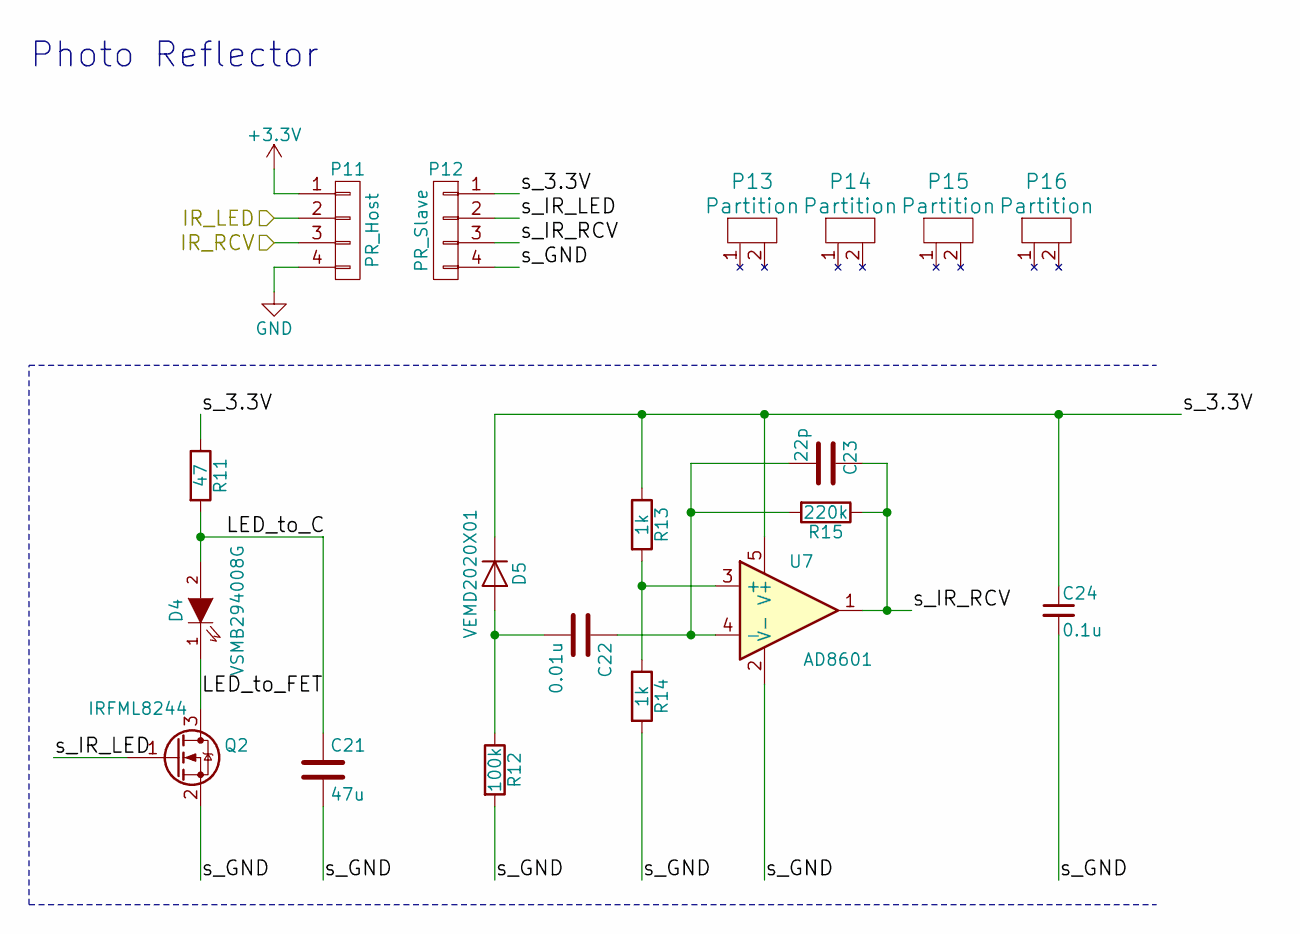
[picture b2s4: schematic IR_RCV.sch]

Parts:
C17: 47u; C_0805
C18: 0.01u; C_0201
C19: 22p; C_0201
C20: 0.1u; C_0201
D2: VSMB294008G; VISHAY_DIODE
D3: VEMD2020X01; VISHAY_DIODE
P5: PR_Host; STAND_PR_HOST
P6: PR_Slave; STAND_PR_SLAVE
P7, P8, P9, P10: Partition
Q1: IRFML8244; SOT-23
R6: 47; R_0603
R7: 100k; R_0201
R8, R9: 1k; R_0201
R10: 220k; R_0201
U6: AD8601; SOT-23-5

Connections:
+3V3: P5.1; also elsewhere on the board
/IR_RCV_SL/LED_to_C: C17.1, D2.2 (A), R6.2
/IR_RCV_SL/LED_to_FET: D2.1 (K), Q1.3 (D)
/IR_RCV_SL/s_3.3V: C20.1, D3.1 (K), P6.1, R6.1, R8.1, U6.5 (V+)
/IR_RCV_SL/s_GND: C17.2, C20.2, P6.4, Q1.2 (S), R7.2, R9.2, U6.2 (V-)
/IR_RCV_SL/s_IR_LED: P6.2, Q1.1 (G)
/IR_RCV_SL/s_IR_RCV: C19.1, P6.3, R10.1, U6.1
GND: P5.4; also elsewhere on the board
unnamed: C18.1, C19.2, R10.2, U6.4 (-)
unnamed: C18.2, D3.2 (A), R7.1
unnamed: R8.2, R9.1, U6.3 (+)
PR-LED-L: P5.2; also elsewhere on the board
PR-RCV-L: P5.3; also elsewhere on the board

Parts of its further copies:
C21: 47u; C_0805
C22: 0.01u; C_0201
C23: 22p; C_0201
C24: 0.1u; C_0201
D4: VSMB294008G; VISHAY_DIODE
D5: VEMD2020X01; VISHAY_DIODE
P11: PR_Host; STAND_PR_HOST
P12: PR_Slave; STAND_PR_SLAVE
P13, P14, P15: Partition
Q2: IRFML8244; SOT-23
R11: 47; R_0603
R12: 100k; R_0201
R13, R14: 1k; R_0201
R15: 220k; R_0201
U7: AD8601; SOT-23-5

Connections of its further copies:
+3V3: P11.1; also elsewhere on the board
/IR_RCV_SR/LED_to_C: C21.1, D4.2 (A), R11.2
/IR_RCV_SR/LED_to_FET: D4.1 (K), Q2.3 (D)
/IR_RCV_SR/s_3.3V: C24.1, D5.1 (K), P12.1, R11.1, R13.1, U7.5 (V+)
/IR_RCV_SR/s_GND: C21.2, C24.2, P12.4, Q2.2 (S), R12.2, R14.2, U7.2 (V-)
/IR_RCV_SR/s_IR_LED: P12.2, Q2.1 (G)
/IR_RCV_SR/s_IR_RCV: C23.1, P12.3, R15.1, U7.1
GND: P11.4; also elsewhere on the board
unnamed: C22.1, C23.2, R15.2, U7.4 (-)
unnamed: C22.2, D5.2 (A), R12.1
unnamed: R13.2, R14.1, U7.3 (+)
PR-LED-R: P11.2; also elsewhere on the board
PR-RCV-R: P11.3; also elsewhere on the board

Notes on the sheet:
Photo Reflector
